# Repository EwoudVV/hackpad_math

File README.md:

# hackpad_math
A 20-key macropad to type special math characters that you normally cannot type on a standard keyboard.

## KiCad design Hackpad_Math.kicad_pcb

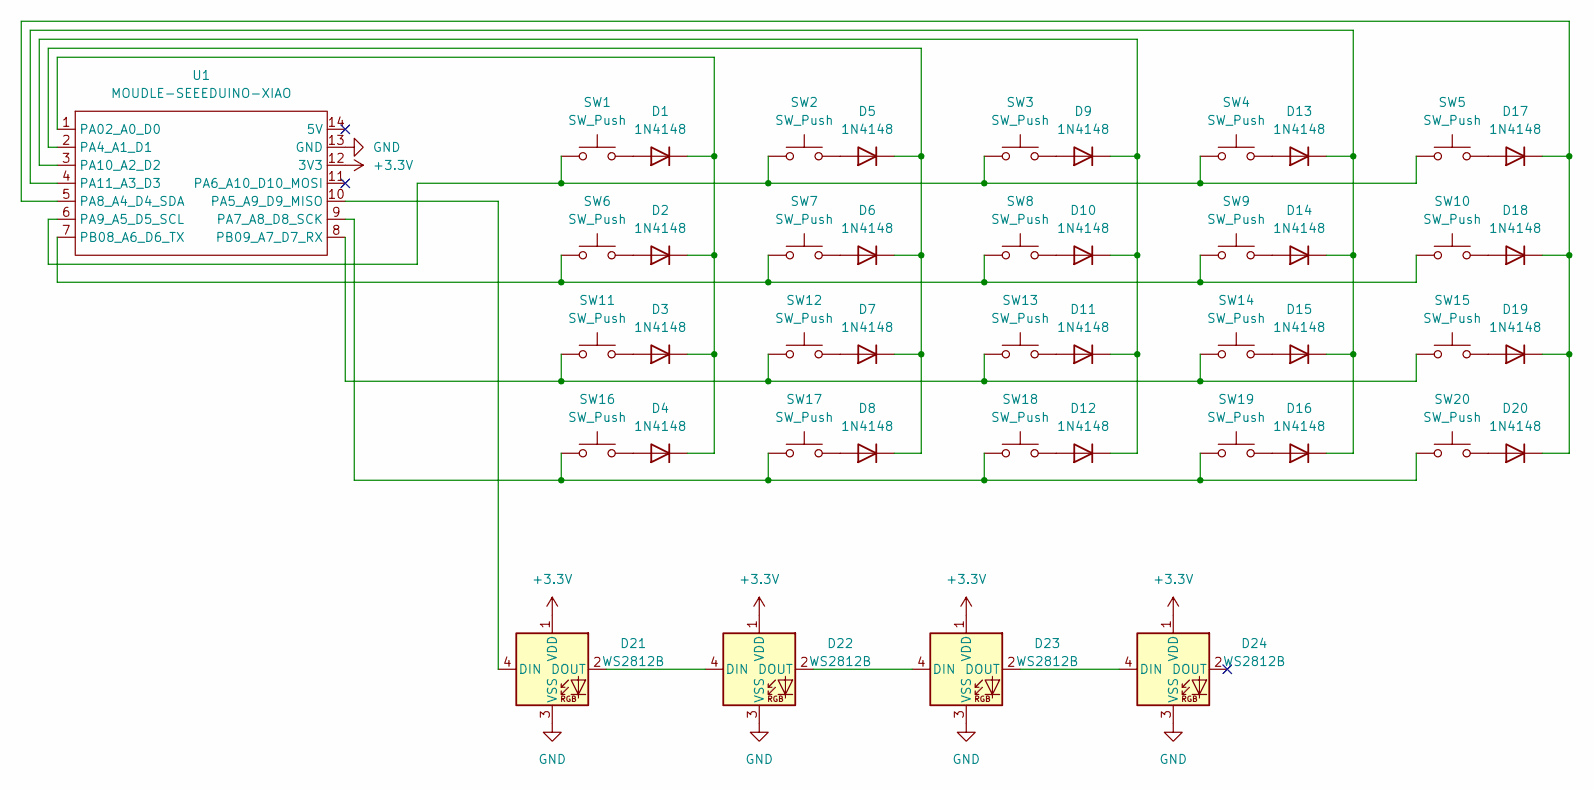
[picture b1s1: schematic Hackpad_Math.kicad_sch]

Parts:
D1, D2, D3, D4, D5, D6, D7, D8, D9, D10, D11, D12, D13, D14, D15, D16, D17, D18, D19, D20: 1N4148; D_DO-35_SOD27_P7.62mm_Horizontal
D21, D22, D23, D24: WS2812B; LED_WS2812B_PLCC4_5.0x5.0mm_P3.2mm
SW1, SW2, SW3, SW4, SW5, SW6, SW7, SW8, SW9, SW10, SW11, SW12, SW13, SW14, SW15, SW16, SW17, SW18, SW19, SW20: SW_Push; Gateron-KS33-Solderable-1U
U1: MOUDLE-SEEEDUINO-XIAO; XIAO-Generic-Thruhole-14P-2.54-21X17.8MM

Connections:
+3.3V: D21.1 (VDD), D22.1 (VDD), D23.1 (VDD), D24.1 (VDD), U1.12 (3V3)
GND: D21.3 (VSS), D22.3 (VSS), D23.3 (VSS), D24.3 (VSS), U1.13 (GND)
unnamed: D1.2 (A), SW1.2
unnamed: D1.1 (K), D2.1 (K), D3.1 (K), D4.1 (K), U1.1 (PA02_A0_D0)
unnamed: D2.2 (A), SW6.2
unnamed: D3.2 (A), SW11.2
unnamed: D4.2 (A), SW16.2
unnamed: D5.2 (A), SW2.2
unnamed: D5.1 (K), D6.1 (K), D7.1 (K), D8.1 (K), U1.2 (PA4_A1_D1)
unnamed: D6.2 (A), SW7.2
unnamed: D7.2 (A), SW12.2
unnamed: D8.2 (A), SW17.2
unnamed: D9.2 (A), SW3.2
unnamed: D10.2 (A), SW8.2
unnamed: D9.1 (K), D10.1 (K), D11.1 (K), D12.1 (K), U1.3 (PA10_A2_D2)
unnamed: D11.2 (A), SW13.2
unnamed: D12.2 (A), SW18.2
unnamed: D13.2 (A), SW4.2
unnamed: D13.1 (K), D14.1 (K), D15.1 (K), D16.1 (K), U1.4 (PA11_A3_D3)
unnamed: D14.2 (A), SW9.2
unnamed: D15.2 (A), SW14.2
unnamed: D16.2 (A), SW19.2
unnamed: D17.2 (A), SW5.2
unnamed: D17.1 (K), D18.1 (K), D19.1 (K), D20.1 (K), U1.5 (PA8_A4_D4_SDA)
unnamed: D18.2 (A), SW10.2
unnamed: D19.2 (A), SW15.2
unnamed: D20.2 (A), SW20.2
unnamed: D21.4 (DIN), U1.10 (PA5_A9_D9_MISO)
unnamed: D21.2 (DOUT), D22.4 (DIN)
unnamed: D22.2 (DOUT), D23.4 (DIN)
unnamed: D23.2 (DOUT), D24.4 (DIN)
unnamed: SW16.1, SW17.1, SW18.1, SW19.1, SW20.1, U1.9 (PA7_A8_D8_SCK)
unnamed: SW1.1, SW2.1, SW3.1, SW4.1, SW5.1, U1.6 (PA9_A5_D5_SCL)
unnamed: SW6.1, SW7.1, SW8.1, SW9.1, SW10.1, U1.7 (PB08_A6_D6_TX)
unnamed: SW11.1, SW12.1, SW13.1, SW14.1, SW15.1, U1.8 (PB09_A7_D7_RX)

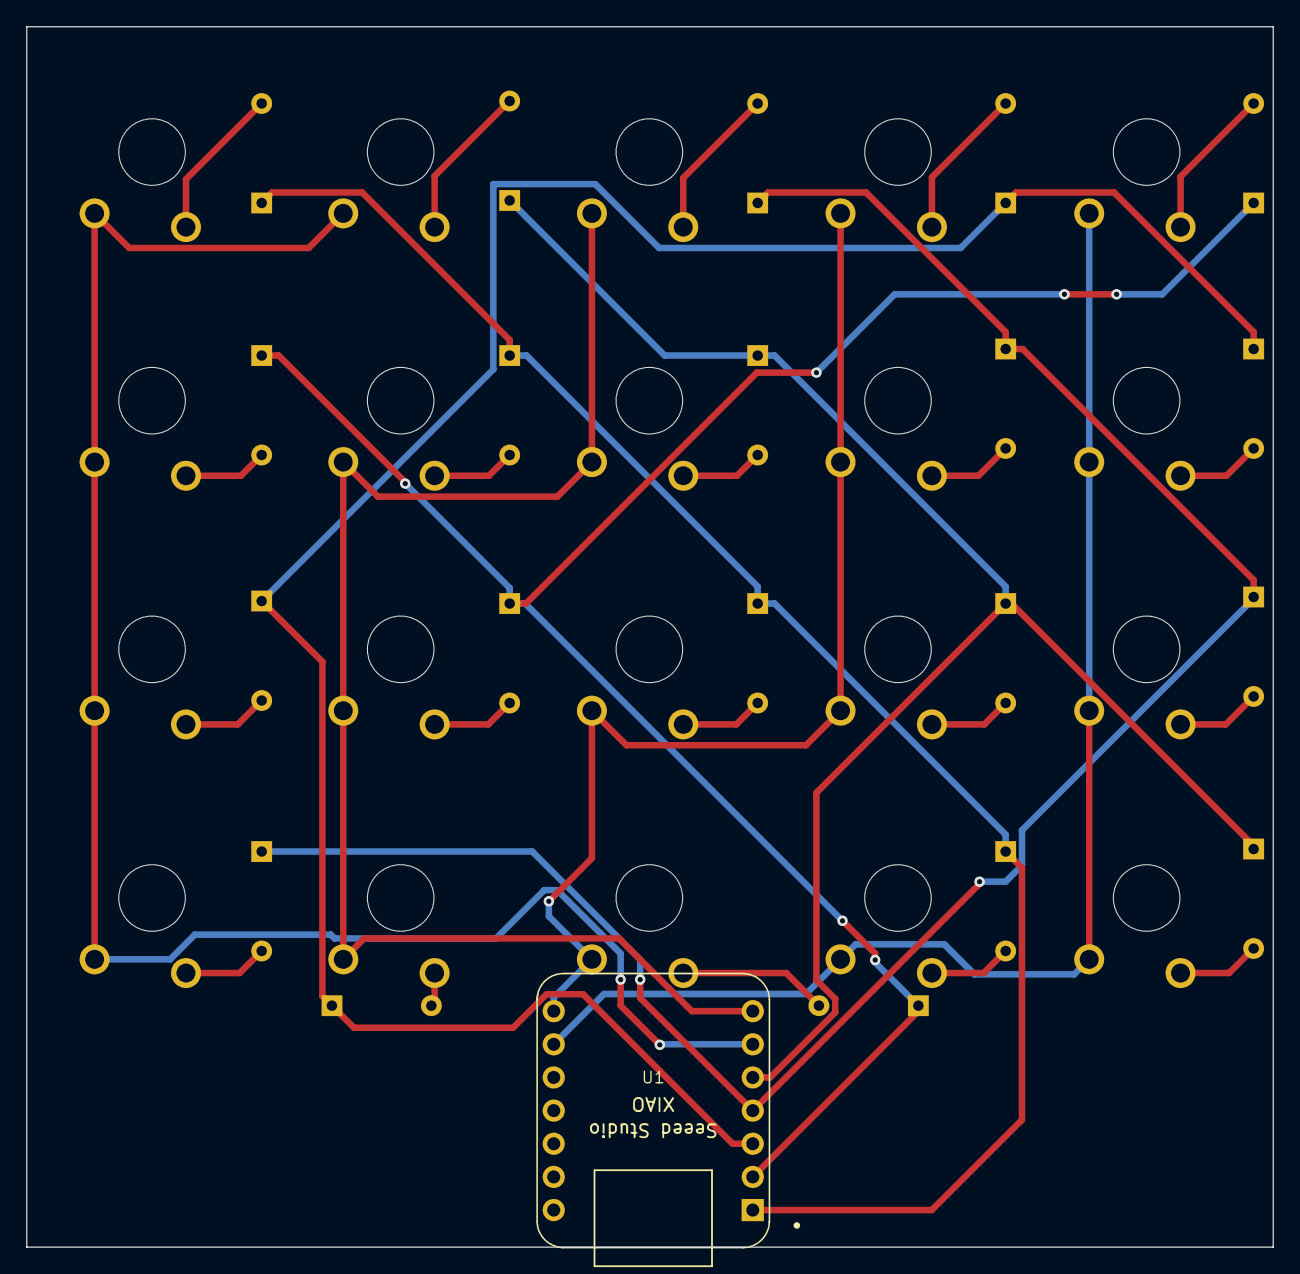
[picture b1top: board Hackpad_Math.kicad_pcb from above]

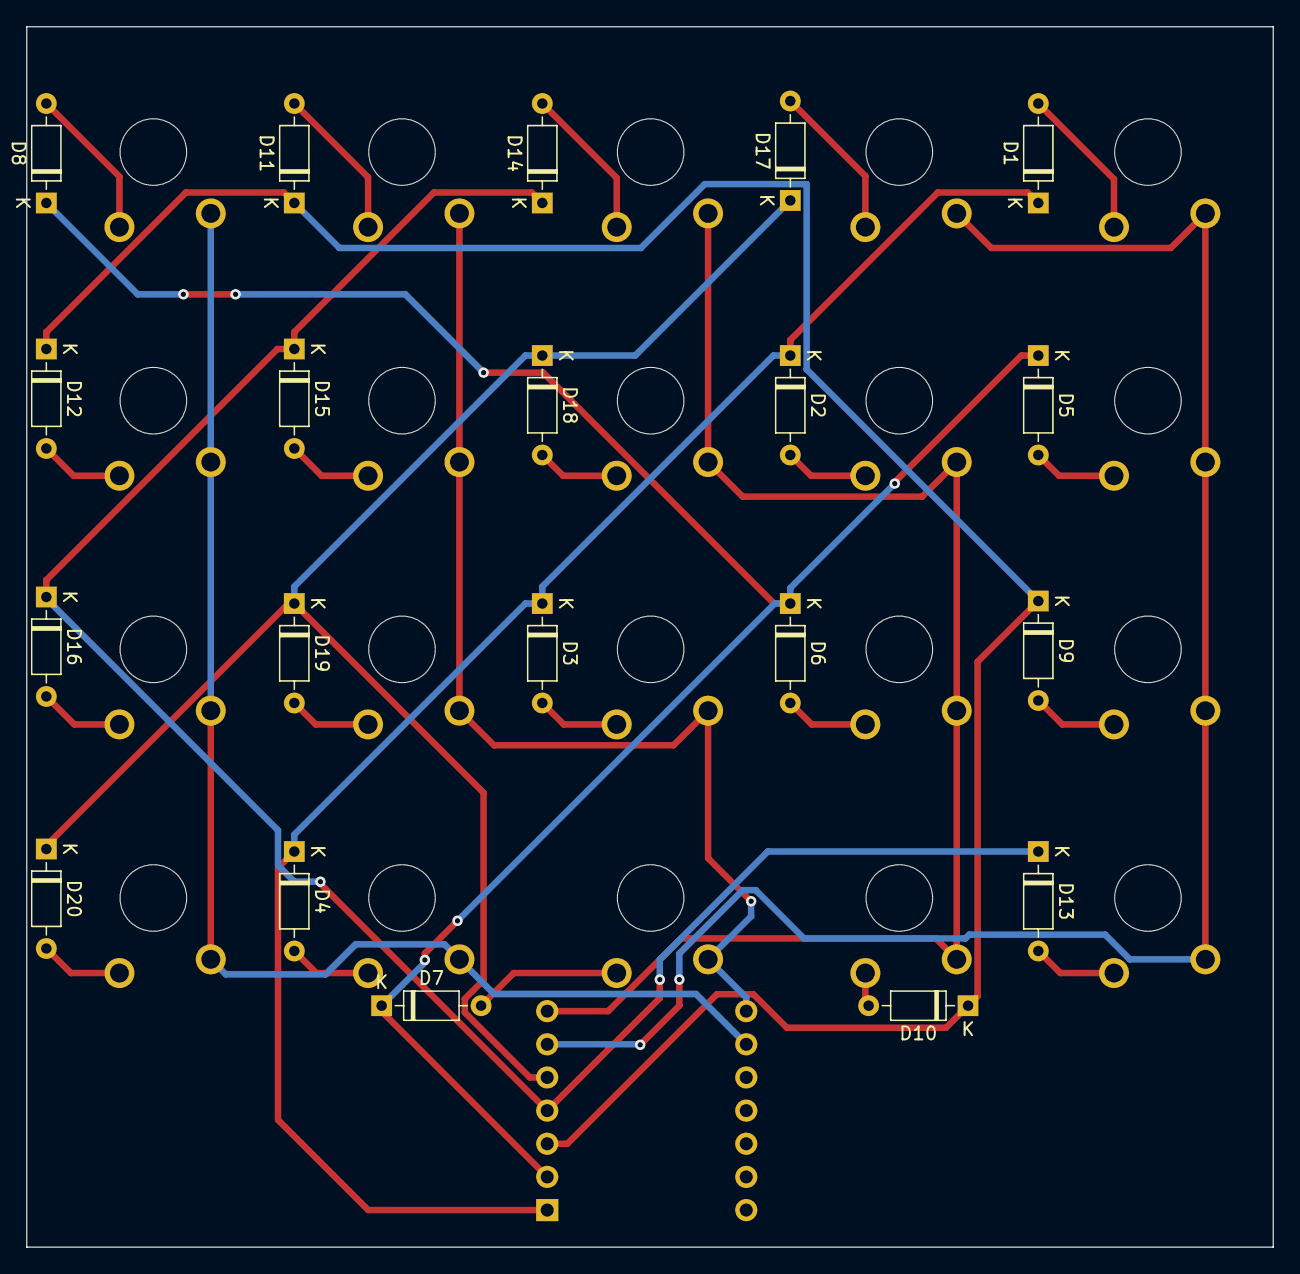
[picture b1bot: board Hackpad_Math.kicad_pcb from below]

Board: 2 copper layers, 95.5 x 93.5 mm, 41 parts (20 on the bottom side), 29 nets.

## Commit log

2024-10-06 Create example
